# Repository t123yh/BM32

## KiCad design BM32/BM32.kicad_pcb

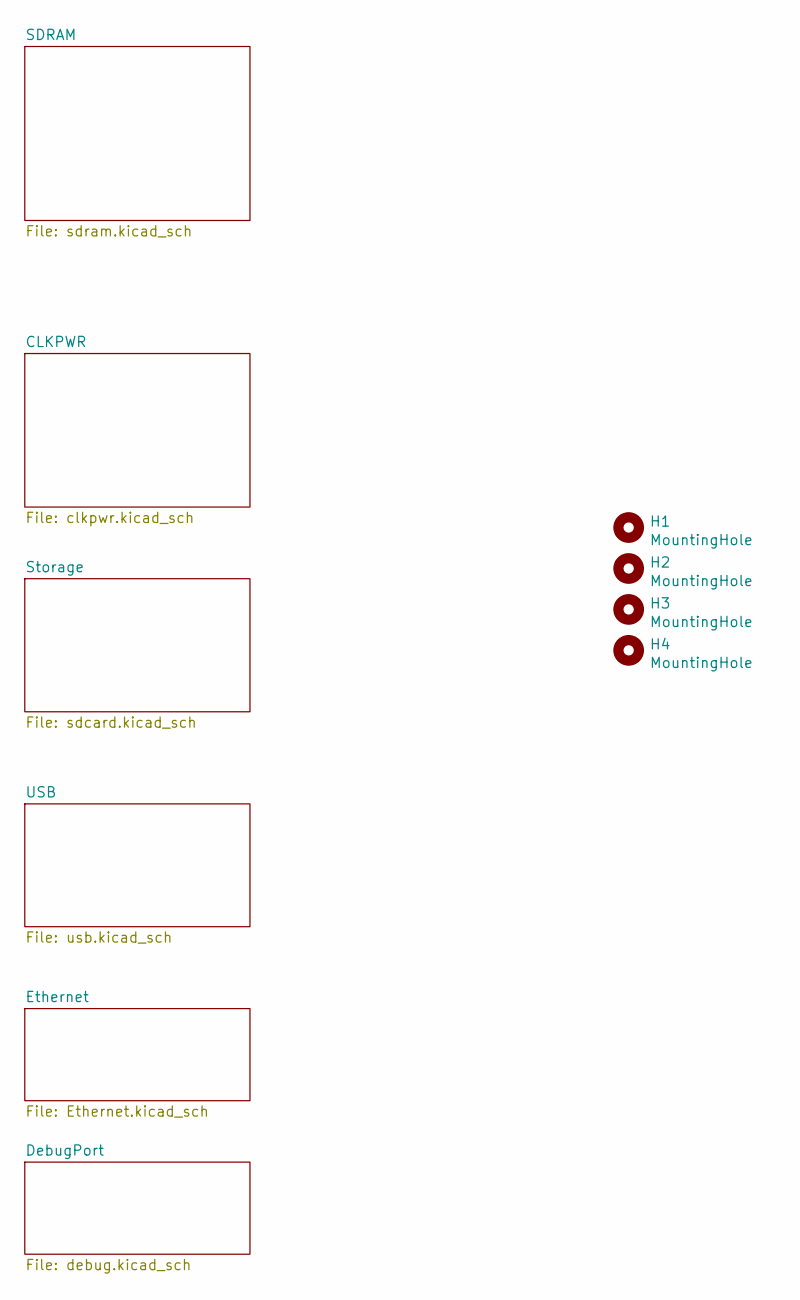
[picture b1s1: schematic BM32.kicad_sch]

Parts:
H1, H2, H3, H4: MountingHole; MountingHole_3.2mm_M3

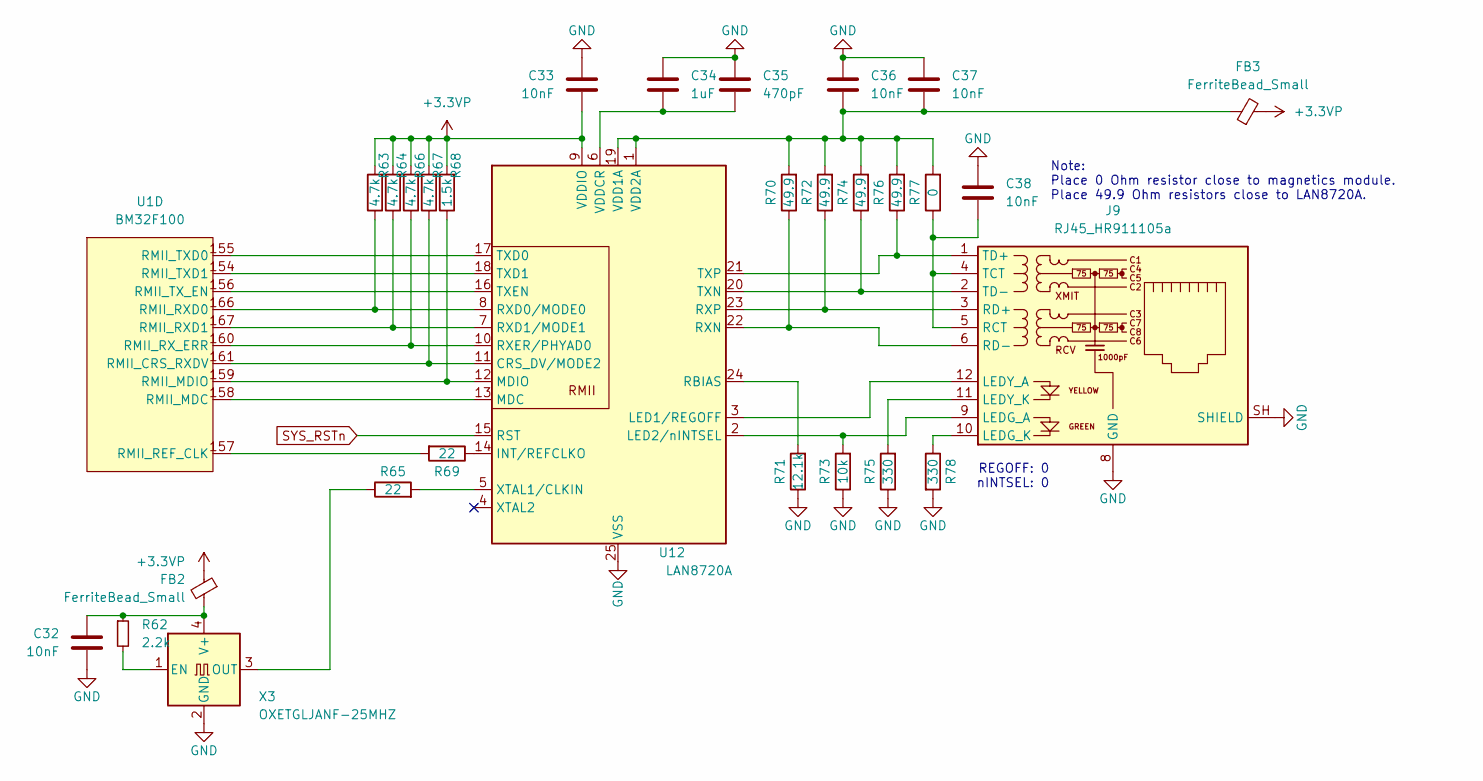
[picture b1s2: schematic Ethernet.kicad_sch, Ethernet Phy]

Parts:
C32, C33, C36, C37, C38: 10nF; 0402_C
C34: 1uF; 0402_C
C35: 470pF; 0402_C
FB2, FB3: FerriteBead_Small; 0805_L
J9: RJ45_HR911105a; RJ45_Hanrun_HR911105A
R62: 2.2k; 0402_R
R63, R64, R66, R67: 4.7k; 0402_R
R65, R69: 22; 0402_R
R68: 1.5k; 0402_R
R70, R72, R74, R76: 49.9; 0402_R
R71: 12.1k; 0402_R
R73: 10k; 0402_R
R75, R78: 330; 0402_R
R77: 0; 0402_R
U1: BM32F100; VQFP-176_20x20mm_P0.4mm
U12: LAN8720A; QFN-24-1EP_4x4mm_P0.5mm_EP2.6x2.6mm_ThermalVias
X3: OXETGLJANF-25MHZ; SMD-3225_4P

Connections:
+3.3VP: C33.2, FB2.1, FB3.2, R63.2, R64.2, R66.2, R67.2, R68.2, U12.9 (VDDIO); also elsewhere on the board
GND: C32.1, C33.1, C34.1, C35.1, C36.1, C37.1, C38.1, J9.8 (GND), J9.SH (SHIELD), R71.1, R73.1, R75.1, R78.2, U12.25 (VSS), X3.2 (GND); also elsewhere on the board
unnamed: C32.2, FB2.2, R62.1, X3.4 (V+)
unnamed: C34.2, C35.2, U12.6 (VDDCR)
unnamed: C36.2, C37.2, FB3.1, R70.2, R72.2, R74.2, R76.2, R77.2, U12.1 (VDD2A), U12.19 (VDD1A)
unnamed: C38.2, J9.4 (TCT), J9.5 (RCT), R77.1
unnamed: J9.1 (TD+), R76.1, U12.21 (TXP)
unnamed: J9.2 (TD-), R74.1, U12.20 (TXN)
unnamed: J9.3 (RD+), R72.1, U12.23 (RXP)
unnamed: J9.6 (RD-), R70.1, U12.22 (RXN)
unnamed: J9.9 (LEDG_A), R73.2, U12.2 (LED2/nINTSEL)
unnamed: J9.10 (LEDG_K), R78.1
unnamed: J9.11 (LEDY_K), R75.2
unnamed: J9.12 (LEDY_A), U12.3 (LED1/REGOFF)
unnamed: R62.2, X3.1 (EN)
unnamed: R63.1, U1.166 (RMII_RXD0), U12.8 (RXD0/MODE0)
unnamed: R64.1, U1.167 (RMII_RXD1), U12.7 (RXD1/MODE1)
unnamed: R65.1, X3.3 (OUT)
unnamed: R65.2, U12.5 (XTAL1/CLKIN)
unnamed: R66.1, U1.160 (RMII_RX_ERR), U12.10 (RXER/PHYAD0)
unnamed: R67.1, U1.161 (RMII_CRS_RXDV), U12.11 (CRS_DV/MODE2)
unnamed: R68.1, U1.159 (RMII_MDIO), U12.12 (MDIO)
unnamed: R69.1, U12.14 (INT/REFCLKO)
unnamed: R69.2, U1.157 (RMII_REF_CLK)
unnamed: R71.2, U12.24 (RBIAS)
unnamed: U1.154 (RMII_TXD1), U12.18 (TXD1)
unnamed: U1.155 (RMII_TXD0), U12.17 (TXD0)
unnamed: U1.156 (RMII_TX_EN), U12.16 (TXEN)
unnamed: U1.158 (RMII_MDC), U12.13 (MDC)
SYS_RSTn: U12.15 (RST); also elsewhere on the board

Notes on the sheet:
REGOFF: 0 nINTSEL: 0
Note: Place 0 Ohm resistor close to magnetics module. Place 49.9 Ohm resistors close to LAN8720A.

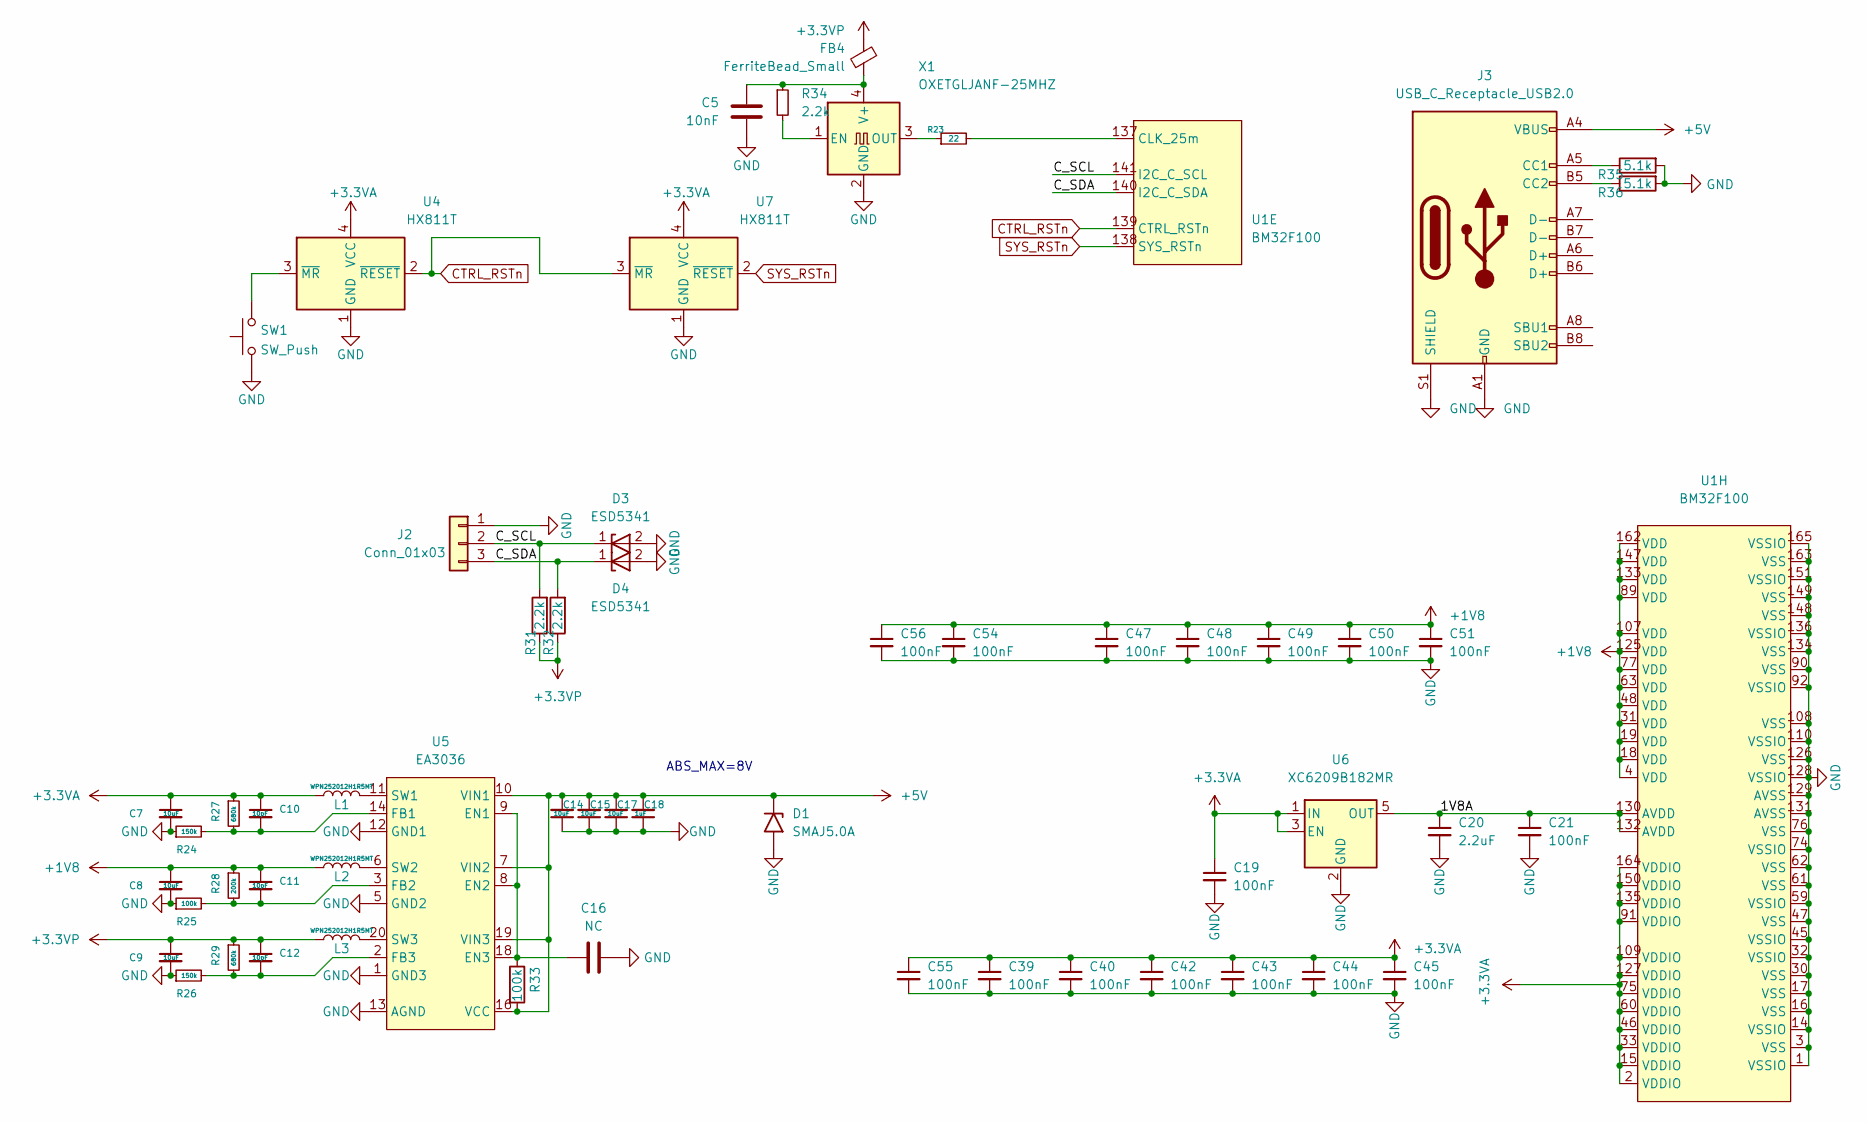
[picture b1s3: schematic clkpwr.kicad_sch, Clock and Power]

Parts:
C5: 10nF; 0402_C
C7, C8, C9, C14, C15, C17: 10uF; 0805_C
C10, C11, C12: 10pF; 0402_C
C16: NC; 0402_C
C18: 1uF; 0402_C
C19, C21, C39, C40, C42, C43, C44, C45, C47, C48, C49, C50, C51, C54, C55, C56: 100nF; 0402_C
C20: 2.2uF; 0402_C
D1: SMAJ5.0A; D_SMA
D3, D4: ESD5341; 0402_R
FB4: FerriteBead_Small; 0805_L
J2: Conn_01x03; PinHeader_1x03_P2.54mm_Vertical
J3: USB_C_Receptacle_USB2.0; USB_C_Receptacle_HRO_TYPE-C-31-M-12
L1, L2, L3: WPN252012H1R5MT; L_1008_2520Metric
R23: 22; 0402_R
R24, R26: 150k; 0402_R
R25, R33: 100k; 0402_R
R27, R29: 680k; 0402_R
R28: 200k; 0402_R
R31, R32, R34: 2.2k; 0402_R
R35, R36: 5.1k; 0402_R
SW1: SW_Push; SW_Push_SPST_NO_Alps_SKRK
U1: BM32F100; VQFP-176_20x20mm_P0.4mm
U4, U7: HX811T; SOT-143
U5: EA3036; QFN-20-1EP_3x3mm_P0.4mm_EP1.65x1.65mm_ThermalVias
U6: XC6209B182MR; SOT-23-5
X1: OXETGLJANF-25MHZ; SMD-3225_4P

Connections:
+1V8: C8.1, C11.1, C47.1, C48.1, C49.1, C50.1, C51.1, C54.1, C56.1, L2.1, R28.1, U1.4 (VDD), U1.18 (VDD), U1.19 (VDD), U1.31 (VDD), U1.48 (VDD), U1.63 (VDD), U1.77 (VDD), U1.89 (VDD), U1.107 (VDD), U1.125 (VDD), U1.133 (VDD), U1.147 (VDD), U1.162 (VDD); also elsewhere on the board
+3.3VA: C7.1, C10.1, C19.1, C39.1, C40.1, C42.1, C43.1, C44.1, C45.1, C55.1, L1.1, R27.1, U1.2 (VDDIO), U1.15 (VDDIO), U1.33 (VDDIO), U1.46 (VDDIO), U1.60 (VDDIO), U1.75 (VDDIO), U1.91 (VDDIO), U1.109 (VDDIO), U1.127 (VDDIO), U1.135 (VDDIO), U1.150 (VDDIO), U1.164 (VDDIO), U4.4 (VCC), U6.1 (IN), U6.3 (EN), U7.4 (VCC); also elsewhere on the board
+3.3VP: C9.1, C12.1, FB4.1, L3.1, R29.1, R31.1, R32.1; also elsewhere on the board
+5V: C14.2, C15.2, C17.2, C18.2, D1.1 (A1), J3.A4 (VBUS), J3.A9 (VBUS), J3.B4 (VBUS), J3.B9 (VBUS), R33.2, U5.7 (VIN2), U5.10 (VIN1), U5.16 (VCC), U5.19 (VIN3); also elsewhere on the board
/CLKPWR/1V8A: C20.1, C21.1, U1.130 (AVDD), U1.132 (AVDD), U6.5 (OUT)
/CLKPWR/C_SCL: D3.1, J2.2, R31.2, U1.141 (I2C_C_SCL)
/CLKPWR/C_SDA: D4.1, J2.3, R32.2, U1.140 (I2C_C_SDA)
CTRL_RSTn: U1.139 (CTRL_RSTn), U4.2 (~RESET), U7.3 (~MR)
GND: C5.1, C7.2, C8.2, C9.2, C14.1, C15.1, C16.2, C17.1, C18.1, C19.2, C20.2, C21.2, C39.2, C40.2, C42.2, C43.2, C44.2, C45.2, C47.2, C48.2, C49.2, C50.2, C51.2, C54.2, C55.2, C56.2, D1.2 (A2), D3.2, D4.2, J2.1, J3.A1 (GND), J3.A12 (GND), J3.B1 (GND), J3.B12 (GND), J3.S1 (SHIELD), R24.1, R25.1, R26.1, R35.2, R36.2, SW1.1, U1.1 (VSSIO), U1.3 (VSS), U1.14 (VSSIO), U1.16 (VSS), U1.17 (VSS), U1.30 (VSS), U1.32 (VSSIO), U1.45 (VSSIO), U1.47 (VSS), U1.59 (VSSIO), U1.61 (VSS), U1.62 (VSS), U1.74 (VSSIO), U1.76 (VSS), U1.90 (VSS), U1.92 (VSSIO), U1.108 (VSS), U1.110 (VSSIO), U1.126 (VSS), U1.128 (VSSIO), U1.129 (AVSS), U1.131 (AVSS), U1.134 (VSS), U1.136 (VSSIO), U1.148 (VSS), U1.149 (VSS), U1.151 (VSSIO), U1.163 (VSS), U1.165 (VSSIO), U4.1 (GND), U5.1 (GND3), U5.4 (AGND), U5.5 (GND2), U5.12 (GND1), U5.13 (AGND), U5.15 (AGND), U5.17 (AGND), U5.21 (EP), U6.2 (GND), U7.1 (GND), X1.2 (GND); also elsewhere on the board
unnamed: C5.2, FB4.2, R34.1, X1.4 (V+)
unnamed: C10.2, R24.2, R27.2, U5.14 (FB1)
unnamed: C11.2, R25.2, R28.2, U5.3 (FB2)
unnamed: C12.2, R26.2, R29.2, U5.2 (FB3)
unnamed: C16.1, R33.1, U5.8 (EN2), U5.9 (EN1), U5.18 (EN3)
unnamed: J3.A5 (CC1), R35.1
unnamed: J3.B5 (CC2), R36.1
unnamed: L1.2, U5.11 (SW1)
unnamed: L2.2, U5.6 (SW2)
unnamed: L3.2, U5.20 (SW3)
unnamed: R23.1, X1.3 (OUT)
unnamed: R23.2, U1.137 (CLK_25m)
unnamed: R34.2, X1.1 (EN)
unnamed: SW1.2, U4.3 (~MR)
SYS_RSTn: U1.138 (SYS_RSTn), U7.2 (~RESET); also elsewhere on the board

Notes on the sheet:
ABS_MAX=8V

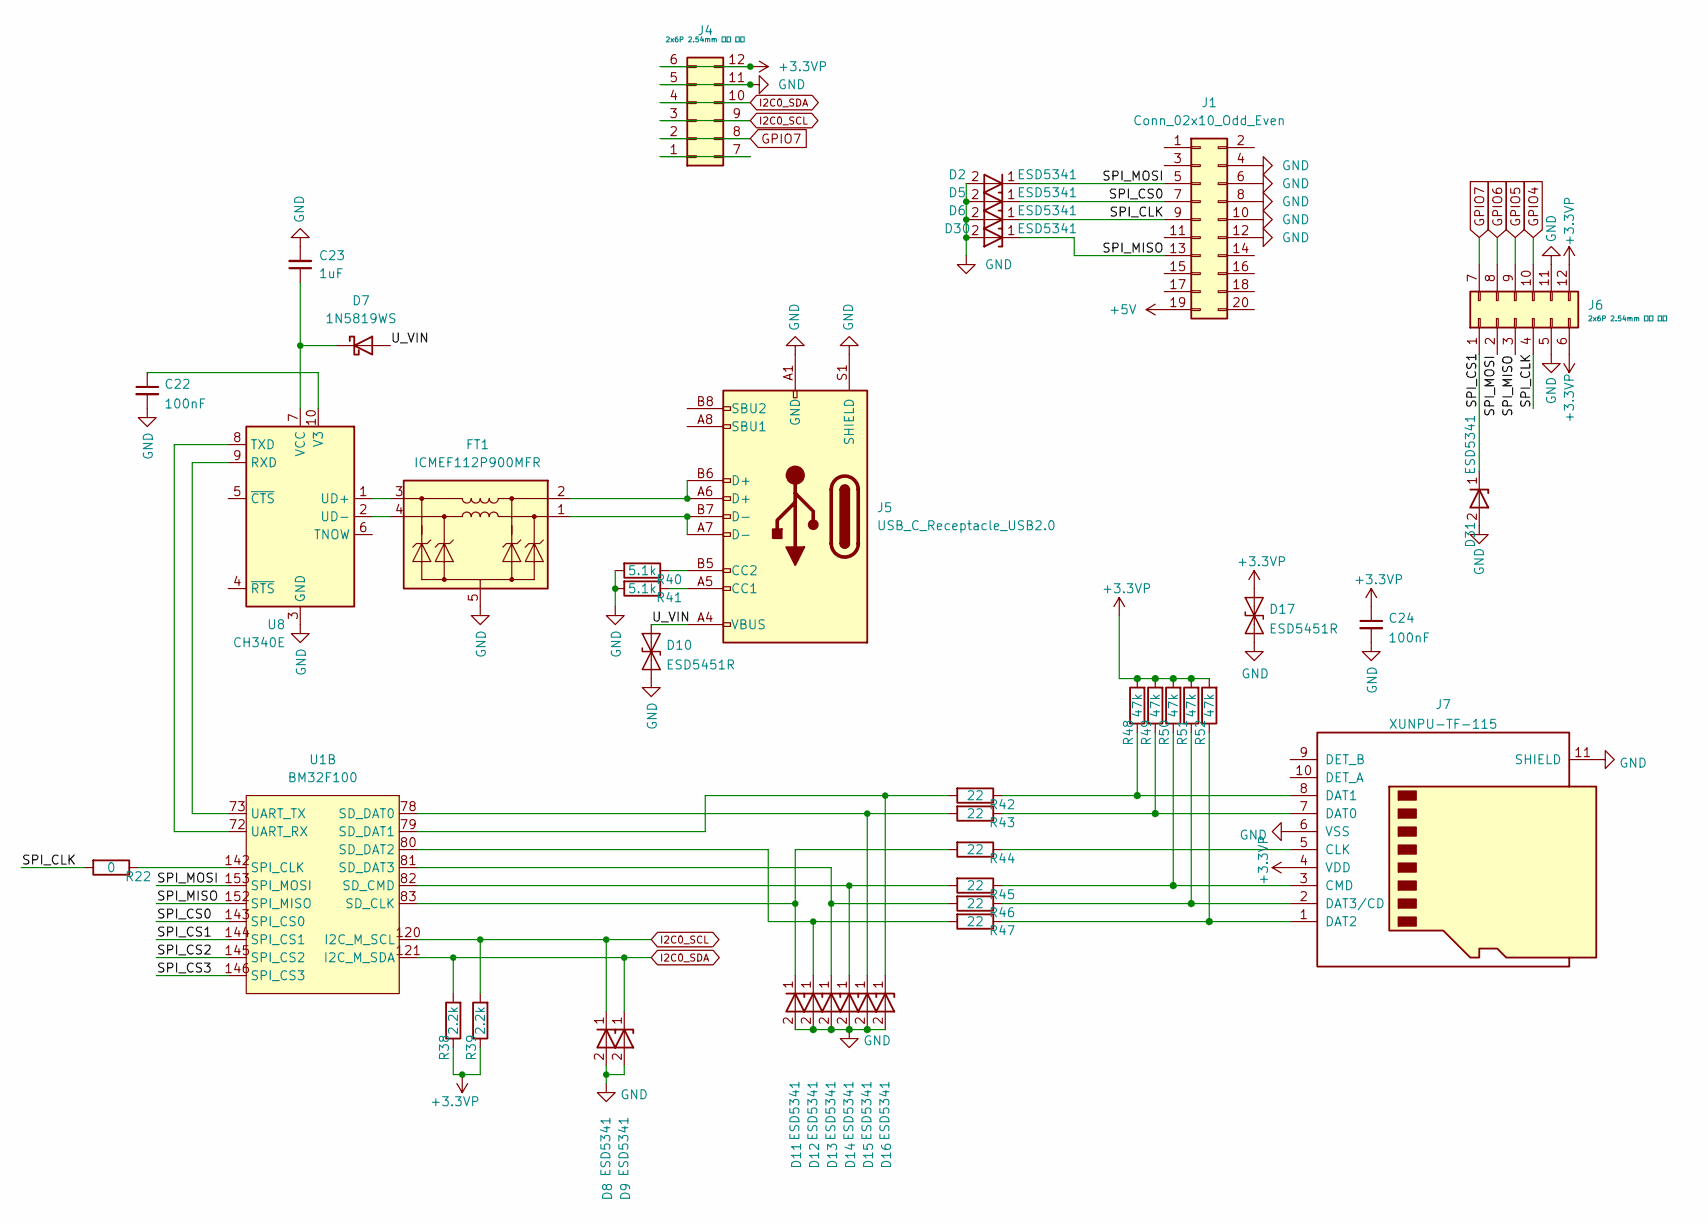
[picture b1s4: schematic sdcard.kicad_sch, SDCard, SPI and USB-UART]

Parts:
C22, C24: 100nF; 0402_C
C23: 1uF; 0402_C
D2, D5, D6, D8, D9, D11, D12, D13, D14, D15, D16, D30, D31: ESD5341; 0402_R
D7: 1N5819WS; SOD-323
D10, D17: ESD5451R; 0402_R
FT1: ICMEF112P900MFR
J1: Conn_02x10_Odd_Even; PinHeader_2x10_P2.54mm_Vertical
J4: 2x6P 2.54mm 弯针 母座; PinSocket_2x06_P2.54mm_Horizontal_PMOD
J5: USB_C_Receptacle_USB2.0; USB_C_Receptacle_HRO_TYPE-C-31-M-12
J6: 2x6P 2.54mm 弯针 母座; PinSocket_2x06_P2.54mm_Vertical_PMOD
J7: XUNPU-TF-115
R22: 0; 0402_R
R38, R39: 2.2k; 0402_R
R40, R41: 5.1k; 0402_R
R42, R43, R44, R45, R46, R47: 22; 0402_R
R48, R49, R50, R51, R52: 47k; 0402_R
U1: BM32F100; VQFP-176_20x20mm_P0.4mm
U8: CH340E; MSOP-10_3x3mm_P0.5mm

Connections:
+3.3VP: C24.1, D17.2 (A2), J4.6, J4.12, J6.6, J6.12, J7.4 (VDD), R38.1, R39.1, R48.2, R49.2, R50.2, R51.2, R52.2; also elsewhere on the board
+5V: J1.19; also elsewhere on the board
/Storage/SPI_CLK: D6.1, J1.9, J6.4, R22.2
/Storage/SPI_CS0: D5.1, J1.7, U1.143 (SPI_CS0)
/Storage/SPI_CS1: D31.1, J6.1, U1.144 (SPI_CS1)
/Storage/SPI_CS2: U1.145 (SPI_CS2)
/Storage/SPI_CS3: U1.146 (SPI_CS3)
/Storage/SPI_MISO: D30.1, J1.13, J6.3, U1.152 (SPI_MISO)
/Storage/SPI_MOSI: D2.1, J1.5, J6.2, U1.153 (SPI_MOSI)
/Storage/U_VIN: D7.2 (A), D10.2 (A2), J5.A4 (VBUS), J5.A9 (VBUS), J5.B4 (VBUS), J5.B9 (VBUS)
GND: C22.2, C23.2, C24.2, D2.2, D5.2, D6.2, D8.2, D9.2, D10.1 (A1), D11.2, D12.2, D13.2, D14.2, D15.2, D16.2, D17.1 (A1), D30.2, D31.2, FT1.5 (GND), FT1.6 (GND), J1.4, J1.6, J1.8, J1.10, J1.12, J4.5, J4.11, J5.A1 (GND), J5.A12 (GND), J5.B1 (GND), J5.B12 (GND), J5.S1 (SHIELD), J6.5, J6.11, J7.6 (VSS), J7.11 (SHIELD), R40.2, R41.2, U8.3 (GND); also elsewhere on the board
GPIO4: J6.10; also elsewhere on the board
GPIO5: J6.9; also elsewhere on the board
GPIO6: J6.8; also elsewhere on the board
GPIO7: J4.2, J4.8, J6.7; also elsewhere on the board
I2C0_SCL: D8.1, J4.3, J4.9, R39.2, U1.120 (I2C_M_SCL)
I2C0_SDA: D9.1, J4.4, J4.10, R38.2, U1.121 (I2C_M_SDA)
unnamed: C22.1, U8.10 (V3)
unnamed: C23.1, D7.1 (K), U8.7 (VCC)
unnamed: D11.1, R44.2, U1.83 (SD_CLK)
unnamed: D12.1, R47.2, U1.80 (SD_DAT2)
unnamed: D13.1, R46.2, U1.81 (SD_DAT3)
unnamed: D14.1, R45.2, U1.82 (SD_CMD)
unnamed: D15.1, R43.2, U1.78 (SD_DAT0)
unnamed: D16.1, R42.2, U1.79 (SD_DAT1)
unnamed: FT1.1 (In_1+), J5.A7 (D-), J5.B7 (D-)
unnamed: FT1.2 (In_1-), J5.A6 (D+), J5.B6 (D+)
unnamed: FT1.3 (Out_1-), U8.1 (UD+)
unnamed: FT1.4 (Out_1+), U8.2 (UD-)
unnamed: J4.1, J4.7
unnamed: J5.A5 (CC1), R41.1
unnamed: J5.B5 (CC2), R40.1
unnamed: J7.1 (DAT2), R47.1, R52.1
unnamed: J7.2 (DAT3/CD), R46.1, R51.1
unnamed: J7.3 (CMD), R45.1, R50.1
unnamed: J7.5 (CLK), R44.1
unnamed: J7.7 (DAT0), R43.1, R49.1
unnamed: J7.8 (DAT1), R42.1, R48.1
unnamed: R22.1, U1.142 (SPI_CLK)
unnamed: U1.72 (UART_RX), U8.8 (TXD)
unnamed: U1.73 (UART_TX), U8.9 (RXD)

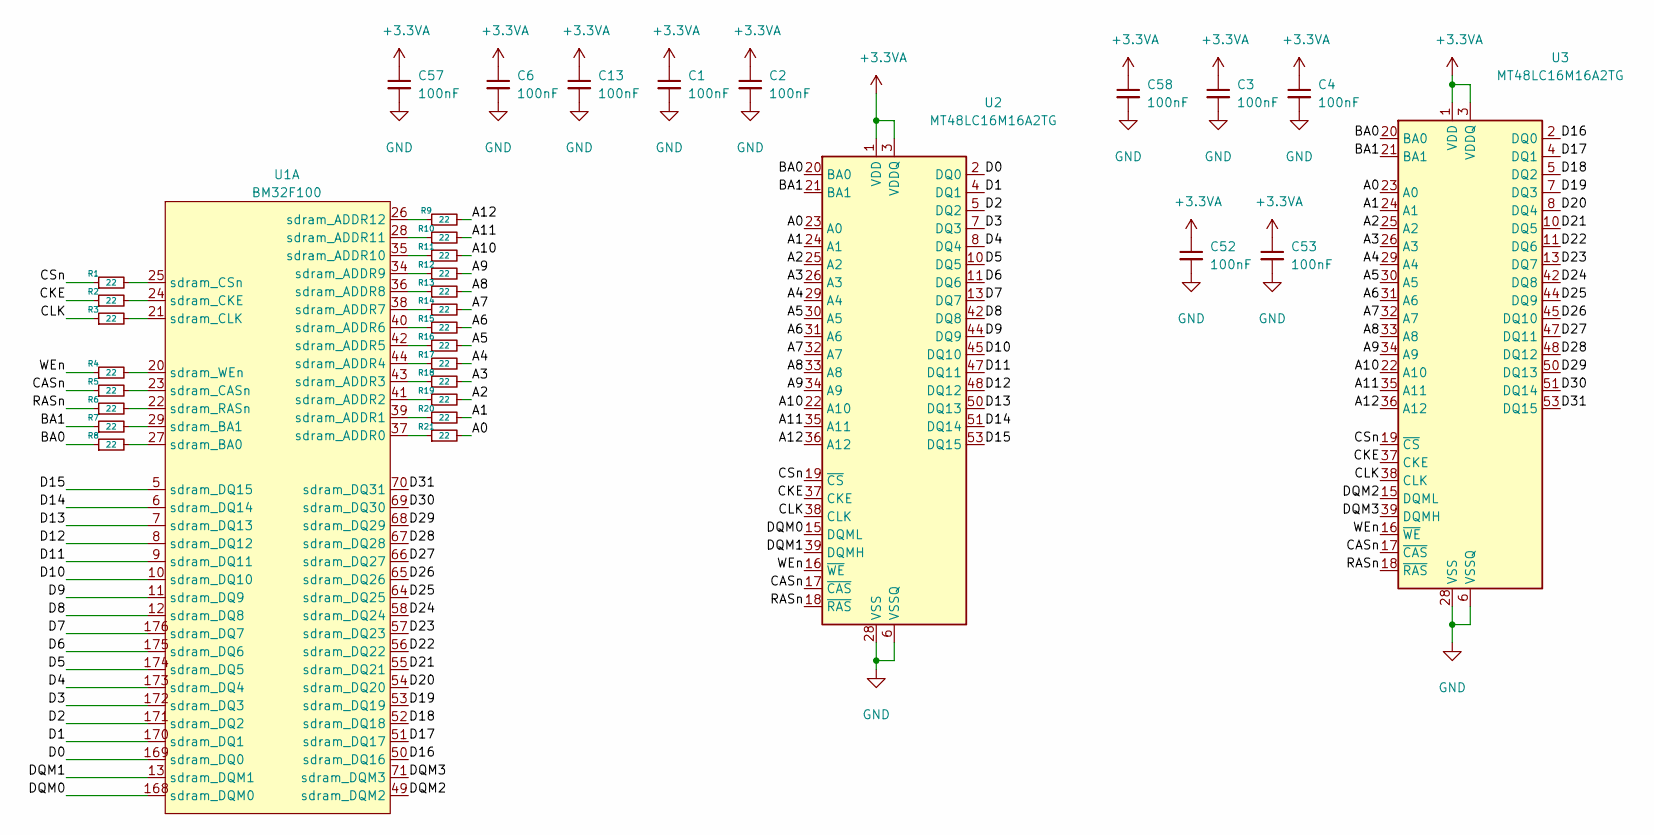
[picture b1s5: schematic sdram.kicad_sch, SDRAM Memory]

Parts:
C1, C2, C3, C4, C6, C13, C52, C53, C57, C58: 100nF; 0402_C
R1, R2, R3, R4, R5, R6, R7, R8, R9, R10, R11, R12, R13, R14, R15, R16, R17, R18, R19, R20, R21: 22; 0402_R
U1: BM32F100; VQFP-176_20x20mm_P0.4mm
U2, U3: MT48LC16M16A2TG; TSOP-II-54_22.2x10.16mm_P0.8mm

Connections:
+3.3VA: C1.1, C2.1, C3.1, C4.1, C6.1, C13.1, C52.1, C53.1, C57.1, C58.1, U2.1 (VDD), U2.3 (VDDQ), U2.9 (VDDQ), U2.14 (VDD), U2.27 (VDD), U2.43 (VDDQ), U2.49 (VDDQ), U3.1 (VDD), U3.3 (VDDQ), U3.9 (VDDQ), U3.14 (VDD), U3.27 (VDD), U3.43 (VDDQ), U3.49 (VDDQ); also elsewhere on the board
/SDRAM/A0: R21.2, U2.23 (A0), U3.23 (A0)
/SDRAM/A1: R20.2, U2.24 (A1), U3.24 (A1)
/SDRAM/A2: R19.2, U2.25 (A2), U3.25 (A2)
/SDRAM/A3: R18.2, U2.26 (A3), U3.26 (A3)
/SDRAM/A4: R17.2, U2.29 (A4), U3.29 (A4)
/SDRAM/A5: R16.2, U2.30 (A5), U3.30 (A5)
/SDRAM/A6: R15.2, U2.31 (A6), U3.31 (A6)
/SDRAM/A7: R14.2, U2.32 (A7), U3.32 (A7)
/SDRAM/A8: R13.2, U2.33 (A8), U3.33 (A8)
/SDRAM/A9: R12.2, U2.34 (A9), U3.34 (A9)
/SDRAM/A10: R11.2, U2.22 (A10), U3.22 (A10)
/SDRAM/A11: R10.2, U2.35 (A11), U3.35 (A11)
/SDRAM/A12: R9.2, U2.36 (A12), U3.36 (A12)
/SDRAM/BA0: R8.1, U2.20 (BA0), U3.20 (BA0)
/SDRAM/BA1: R7.1, U2.21 (BA1), U3.21 (BA1)
/SDRAM/CASn: R5.1, U2.17 (~CAS), U3.17 (~CAS)
/SDRAM/CKE: R2.1, U2.37 (CKE), U3.37 (CKE)
/SDRAM/CLK: R3.1, U2.38 (CLK), U3.38 (CLK)
/SDRAM/CSn: R1.1, U2.19 (~CS), U3.19 (~CS)
/SDRAM/D0: U1.169 (sdram_DQ0), U2.2 (DQ0)
/SDRAM/D1: U1.170 (sdram_DQ1), U2.4 (DQ1)
/SDRAM/D2: U1.171 (sdram_DQ2), U2.5 (DQ2)
/SDRAM/D3: U1.172 (sdram_DQ3), U2.7 (DQ3)
/SDRAM/D4: U1.173 (sdram_DQ4), U2.8 (DQ4)
/SDRAM/D5: U1.174 (sdram_DQ5), U2.10 (DQ5)
/SDRAM/D6: U1.175 (sdram_DQ6), U2.11 (DQ6)
/SDRAM/D7: U1.176 (sdram_DQ7), U2.13 (DQ7)
/SDRAM/D8: U1.12 (sdram_DQ8), U2.42 (DQ8)
/SDRAM/D9: U1.11 (sdram_DQ9), U2.44 (DQ9)
/SDRAM/D10: U1.10 (sdram_DQ10), U2.45 (DQ10)
/SDRAM/D11: U1.9 (sdram_DQ11), U2.47 (DQ11)
/SDRAM/D12: U1.8 (sdram_DQ12), U2.48 (DQ12)
/SDRAM/D13: U1.7 (sdram_DQ13), U2.50 (DQ13)
/SDRAM/D14: U1.6 (sdram_DQ14), U2.51 (DQ14)
/SDRAM/D15: U1.5 (sdram_DQ15), U2.53 (DQ15)
/SDRAM/D16: U1.50 (sdram_DQ16), U3.2 (DQ0)
/SDRAM/D17: U1.51 (sdram_DQ17), U3.4 (DQ1)
/SDRAM/D18: U1.52 (sdram_DQ18), U3.5 (DQ2)
/SDRAM/D19: U1.53 (sdram_DQ19), U3.7 (DQ3)
/SDRAM/D20: U1.54 (sdram_DQ20), U3.8 (DQ4)
/SDRAM/D21: U1.55 (sdram_DQ21), U3.10 (DQ5)
/SDRAM/D22: U1.56 (sdram_DQ22), U3.11 (DQ6)
/SDRAM/D23: U1.57 (sdram_DQ23), U3.13 (DQ7)
/SDRAM/D24: U1.58 (sdram_DQ24), U3.42 (DQ8)
/SDRAM/D25: U1.64 (sdram_DQ25), U3.44 (DQ9)
/SDRAM/D26: U1.65 (sdram_DQ26), U3.45 (DQ10)
/SDRAM/D27: U1.66 (sdram_DQ27), U3.47 (DQ11)
/SDRAM/D28: U1.67 (sdram_DQ28), U3.48 (DQ12)
/SDRAM/D29: U1.68 (sdram_DQ29), U3.50 (DQ13)
/SDRAM/D30: U1.69 (sdram_DQ30), U3.51 (DQ14)
/SDRAM/D31: U1.70 (sdram_DQ31), U3.53 (DQ15)
/SDRAM/DQM0: U1.168 (sdram_DQM0), U2.15 (DQML)
/SDRAM/DQM1: U1.13 (sdram_DQM1), U2.39 (DQMH)
/SDRAM/DQM2: U1.49 (sdram_DQM2), U3.15 (DQML)
/SDRAM/DQM3: U1.71 (sdram_DQM3), U3.39 (DQMH)
/SDRAM/RASn: R6.1, U2.18 (~RAS), U3.18 (~RAS)
/SDRAM/WEn: R4.1, U2.16 (~WE), U3.16 (~WE)
GND: C1.2, C2.2, C3.2, C4.2, C6.2, C13.2, C52.2, C53.2, C57.2, C58.2, U2.6 (VSSQ), U2.12 (VSSQ), U2.28 (VSS), U2.41 (VSS), U2.46 (VSSQ), U2.52 (VSSQ), U2.54 (VSS), U3.6 (VSSQ), U3.12 (VSSQ), U3.28 (VSS), U3.41 (VSS), U3.46 (VSSQ), U3.52 (VSSQ), U3.54 (VSS); also elsewhere on the board
unnamed: R1.2, U1.25 (sdram_CSn)
unnamed: R2.2, U1.24 (sdram_CKE)
unnamed: R3.2, U1.21 (sdram_CLK)
unnamed: R4.2, U1.20 (sdram_WEn)
unnamed: R5.2, U1.23 (sdram_CASn)
unnamed: R6.2, U1.22 (sdram_RASn)
unnamed: R7.2, U1.29 (sdram_BA1)
unnamed: R8.2, U1.27 (sdram_BA0)
unnamed: R9.1, U1.26 (sdram_ADDR12)
unnamed: R10.1, U1.28 (sdram_ADDR11)
unnamed: R11.1, U1.35 (sdram_ADDR10)
unnamed: R12.1, U1.34 (sdram_ADDR9)
unnamed: R13.1, U1.36 (sdram_ADDR8)
unnamed: R14.1, U1.38 (sdram_ADDR7)
unnamed: R15.1, U1.40 (sdram_ADDR6)
unnamed: R16.1, U1.42 (sdram_ADDR5)
unnamed: R17.1, U1.44 (sdram_ADDR4)
unnamed: R18.1, U1.43 (sdram_ADDR3)
unnamed: R19.1, U1.41 (sdram_ADDR2)
unnamed: R20.1, U1.39 (sdram_ADDR1)
unnamed: R21.1, U1.37 (sdram_ADDR0)

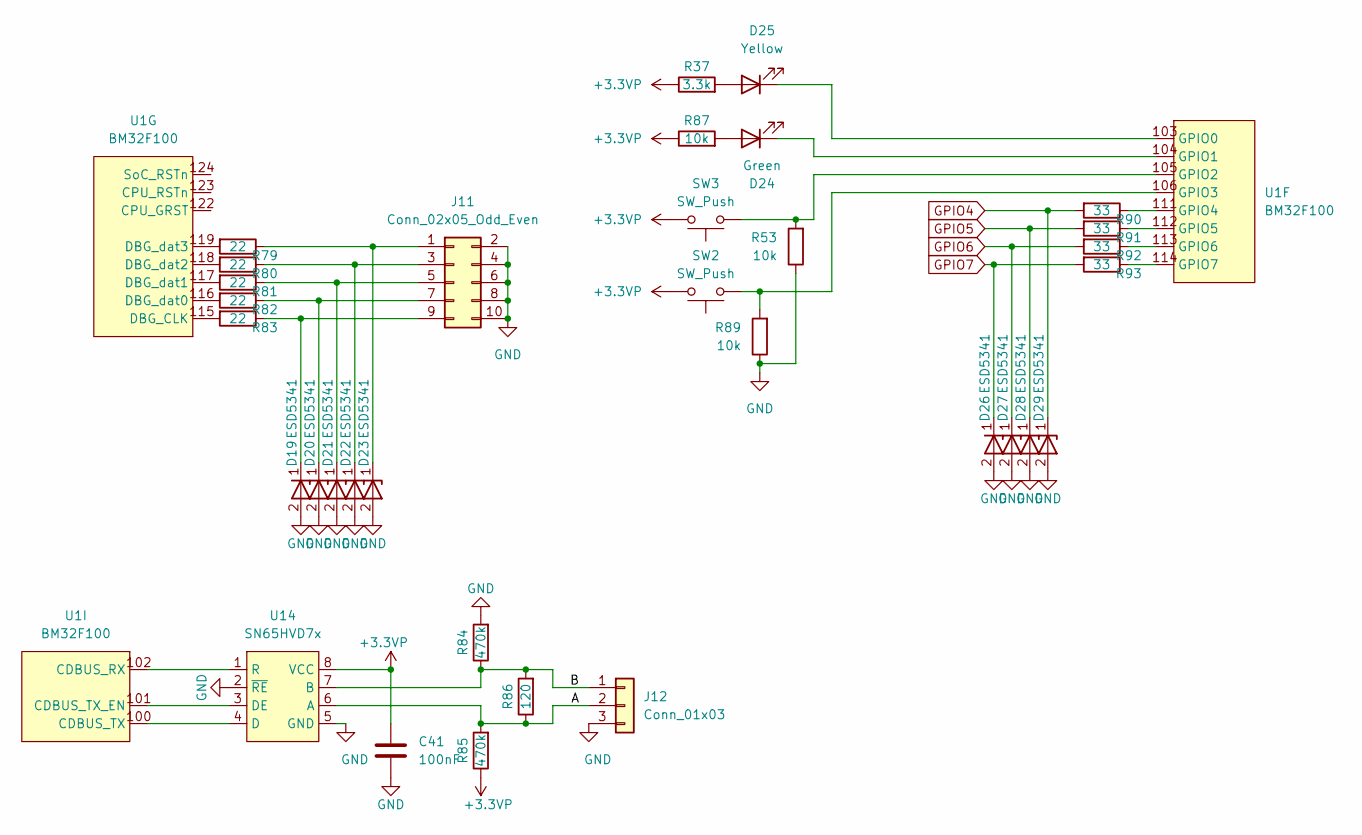
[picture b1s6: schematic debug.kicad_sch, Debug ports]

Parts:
C41: 100nF; 0402_C
D19, D20, D21, D22, D23, D26, D27, D28, D29: ESD5341; 0402_R
D24: Green; 0805_LED_S1_NUM
D25: Yellow; 0805_LED_S1_NUM
J11: Conn_02x05_Odd_Even; PinHeader_2x05_P1.27mm_Vertical
J12: Conn_01x03; PinSocket_1x03_P2.54mm_Vertical
R37: 3.3k; 0402_R
R53, R87, R89: 10k; 0402_R
R79, R80, R81, R82, R83: 22; 0402_R
R84, R85: 470k; 0402_R
R86: 120; 0402_R
R90, R91, R92, R93: 33; 0402_R
SW2, SW3: SW_Push; SW_Push_SPST_NO_Alps_SKRK
U1: BM32F100; VQFP-176_20x20mm_P0.4mm
U14: SN65HVD7x; SOIC-8_3.9x4.9mm_P1.27mm

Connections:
+3.3VP: C41.1, R37.1, R85.1, R87.1, SW2.2, SW3.2, U14.8 (VCC); also elsewhere on the board
/DebugPort/A: J12.2, R85.2, R86.1, U14.6 (A)
/DebugPort/B: J12.1, R84.1, R86.2, U14.7 (B)
GND: C41.2, D19.2, D20.2, D21.2, D22.2, D23.2, D26.2, D27.2, D28.2, D29.2, J11.2, J11.4, J11.6, J11.8, J11.10, J12.3, R53.1, R84.2, R89.1, U14.2 (~RE), U14.5 (GND), U14.9 (GND); also elsewhere on the board
GPIO4: D29.1, R90.2; also elsewhere on the board
GPIO5: D28.1, R91.2; also elsewhere on the board
GPIO6: D27.1, R92.2; also elsewhere on the board
GPIO7: D26.1, R93.2; also elsewhere on the board
unnamed: D19.1, J11.9, R83.1
unnamed: D20.1, J11.7, R82.1
unnamed: D21.1, J11.5, R81.1
unnamed: D22.1, J11.3, R80.1
unnamed: D23.1, J11.1, R79.1
unnamed: D24.1 (K), U1.104 (GPIO1)
unnamed: D24.2 (A), R87.2
unnamed: D25.2 (A), R37.2
unnamed: R79.2, U1.119 (DBG_dat3)
unnamed: R80.2, U1.118 (DBG_dat2)
unnamed: R81.2, U1.117 (DBG_dat1)
unnamed: R82.2, U1.116 (DBG_dat0)
unnamed: R83.2, U1.115 (DBG_CLK)
unnamed: R89.2, SW2.1, U1.106 (GPIO3)
unnamed: R90.1, U1.111 (GPIO4)
unnamed: R91.1, U1.112 (GPIO5)
unnamed: R92.1, U1.113 (GPIO6)
unnamed: R93.1, U1.114 (GPIO7)
unnamed: U1.100 (CDBUS_TX), U14.4 (D)
unnamed: U1.101 (CDBUS_TX_EN), U14.3 (DE)
unnamed: U1.102 (CDBUS_RX), U14.1 (R)
unnamed: D25.1 (K), U1.103 (GPIO0)
unnamed: R53.2, SW3.1, U1.105 (GPIO2)

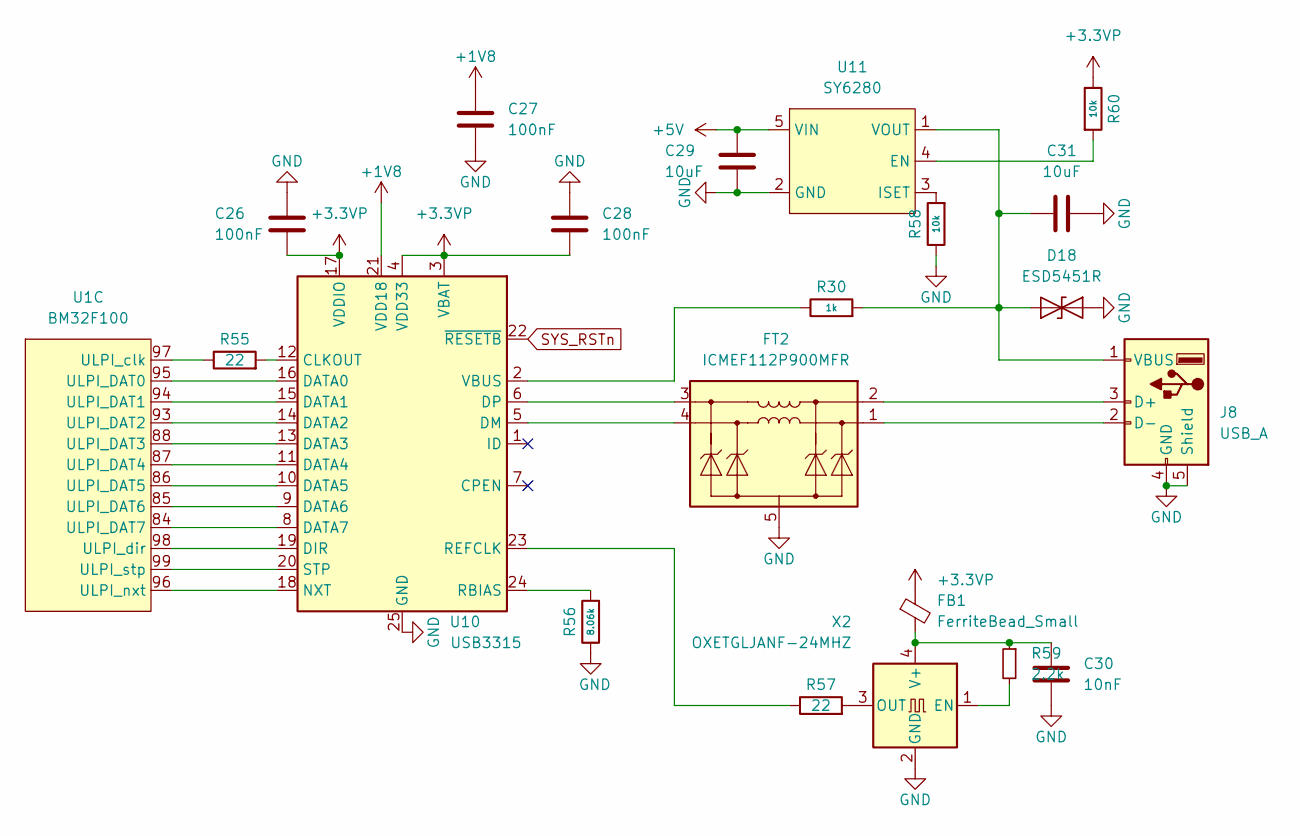
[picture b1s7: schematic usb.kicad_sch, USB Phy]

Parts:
C26, C27, C28: 100nF; 0402_C
C29, C31: 10uF; 0805_C
C30: 10nF; 0402_C
D18: ESD5451R; 0402_R
FB1: FerriteBead_Small; 0805_L
FT2: ICMEF112P900MFR
J8: USB_A; USB_A_Molex_67643_Horizontal; LCSC C2345
R30: 1k; 0402_R
R55, R57: 22; 0402_R
R56: 8.06k; 0402_R
R58, R60: 10k; 0402_R
R59: 2.2k; 0402_R
U1: BM32F100; VQFP-176_20x20mm_P0.4mm
U10: USB3315; QFN-24-1EP_4x4mm_P0.5mm_EP2.6x2.6mm_ThermalVias
U11: SY6280; SOT-23-5
X2: OXETGLJANF-24MHZ; SMD-3225_4P

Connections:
+1V8: C27.2, U10.21 (VDD18); also elsewhere on the board
+3.3VP: C26.2, C28.1, FB1.1, R60.1, U10.3 (VBAT), U10.4 (VDD33), U10.17 (VDDIO); also elsewhere on the board
+5V: C29.1, U11.5 (VIN); also elsewhere on the board
GND: C26.1, C27.1, C28.2, C29.2, C30.1, C31.1, D18.1 (A1), FT2.5 (GND), FT2.6 (GND), J8.4 (GND), J8.5 (Shield), R56.1, R58.1, U10.25 (GND), U11.2 (GND), X2.2 (GND); also elsewhere on the board
unnamed: C30.2, FB1.2, R59.1, X2.4 (V+)
unnamed: C31.2, D18.2 (A2), J8.1 (VBUS), R30.2, U11.1 (VOUT)
unnamed: FT2.1 (In_1+), J8.2 (D-)
unnamed: FT2.2 (In_1-), J8.3 (D+)
unnamed: FT2.3 (Out_1-), U10.6 (DP)
unnamed: FT2.4 (Out_1+), U10.5 (DM)
unnamed: R30.1, U10.2 (VBUS)
unnamed: R55.1, U1.97 (ULPI_clk)
unnamed: R55.2, U10.12 (CLKOUT)
unnamed: R56.2, U10.24 (RBIAS)
unnamed: R57.1, U10.23 (REFCLK)
unnamed: R57.2, X2.3 (OUT)
unnamed: R58.2, U11.3 (ISET)
unnamed: R59.2, X2.1 (EN)
unnamed: R60.2, U11.4 (EN)
unnamed: U1.84 (ULPI_DAT7), U10.8 (DATA7)
unnamed: U1.85 (ULPI_DAT6), U10.9 (DATA6)
unnamed: U1.86 (ULPI_DAT5), U10.10 (DATA5)
unnamed: U1.87 (ULPI_DAT4), U10.11 (DATA4)
unnamed: U1.88 (ULPI_DAT3), U10.13 (DATA3)
unnamed: U1.93 (ULPI_DAT2), U10.14 (DATA2)
unnamed: U1.94 (ULPI_DAT1), U10.15 (DATA1)
unnamed: U1.95 (ULPI_DAT0), U10.16 (DATA0)
unnamed: U1.96 (ULPI_nxt), U10.18 (NXT)
unnamed: U1.98 (ULPI_dir), U10.19 (DIR)
unnamed: U1.99 (ULPI_stp), U10.20 (STP)
SYS_RSTn: U10.22 (~RESETB); also elsewhere on the board

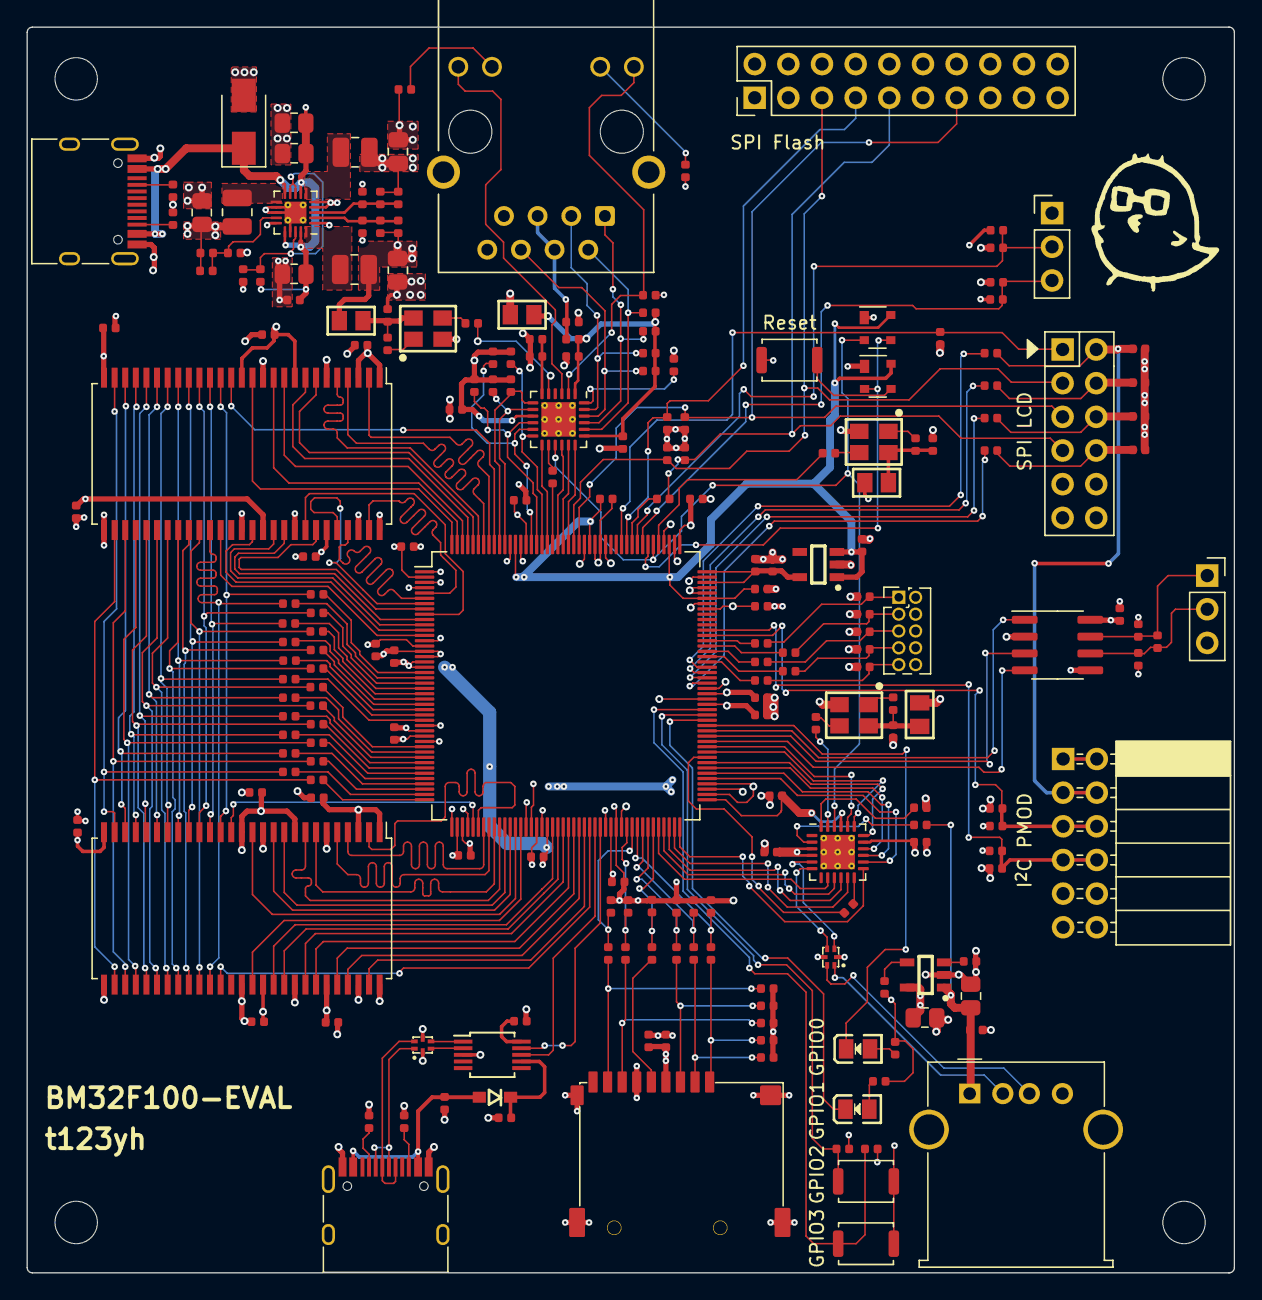
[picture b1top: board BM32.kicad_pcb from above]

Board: 4 copper layers, 91.1 x 94.0 mm, 219 parts (0 on the bottom side), 216 nets.

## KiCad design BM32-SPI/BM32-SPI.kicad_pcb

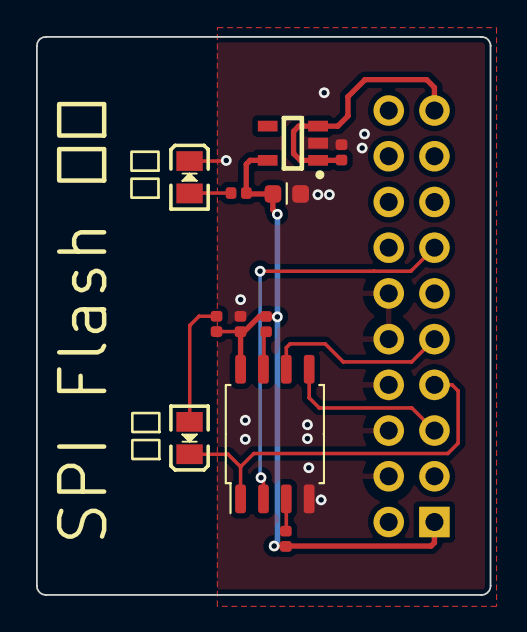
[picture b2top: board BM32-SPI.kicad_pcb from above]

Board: 2 copper layers, 25.2 x 31.0 mm, 12 parts (1 on the bottom side), 11 nets.

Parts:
C1, C3: 100nF; 0402_C
C2: 2.2uF; 0603_C
D1: Green; 0805_LED_S1_NUM
D2: Red; 0805_LED_S1_NUM
J1: PinSocket_2x10_P2.54mm_Vertical
R1, R2: 2.2k; 0402_R
R3: 22k; 0402_R
R4: 6.8k; 0402_R
U1: XC6209F332MR; SOT-23-5
U2: W25Q32JVSS; SOIC-8_5.23x5.23mm_P1.27mm

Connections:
+3.3VP: C2.2, C3.1, J1.1, R1.2, R2.2, R3.2, R4.1, U1.5 (OUT), U2.8 (VCC)
+5V: C1.1, J1.19, U1.1 (IN), U1.3 (EN)
/SPI_CLK: J1.9, U2.6 (CLK)
/SPI_CS0: D2.1 (K), J1.7, U2.1 (~CS)
/SPI_MISO: J1.13, U2.2 (DO(IO1))
/SPI_MOSI: J1.5, U2.5 (DI(IO0))
GND: C1.2, C2.1, C3.2, D1.1 (K), J1.4, J1.6, J1.8, J1.10, J1.12, U1.2 (GND), U2.4 (GND)
unnamed: D2.2 (A), R4.2
unnamed: R1.1, U2.3 (IO2)
unnamed: R2.1, U2.7 (IO3)
unnamed: D1.2 (A), R3.1

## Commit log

2022-04-25 Remove PDf
